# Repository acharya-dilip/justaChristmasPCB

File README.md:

# JustaChristmasPCB
This is a PCB with alternating green and red lights that turn on and off with a 0.6 second delay and has a hugeee snowflake in the back that'll be a challenge to me when I start soldering ;-;

# Schematic

# PCB

# 3D View

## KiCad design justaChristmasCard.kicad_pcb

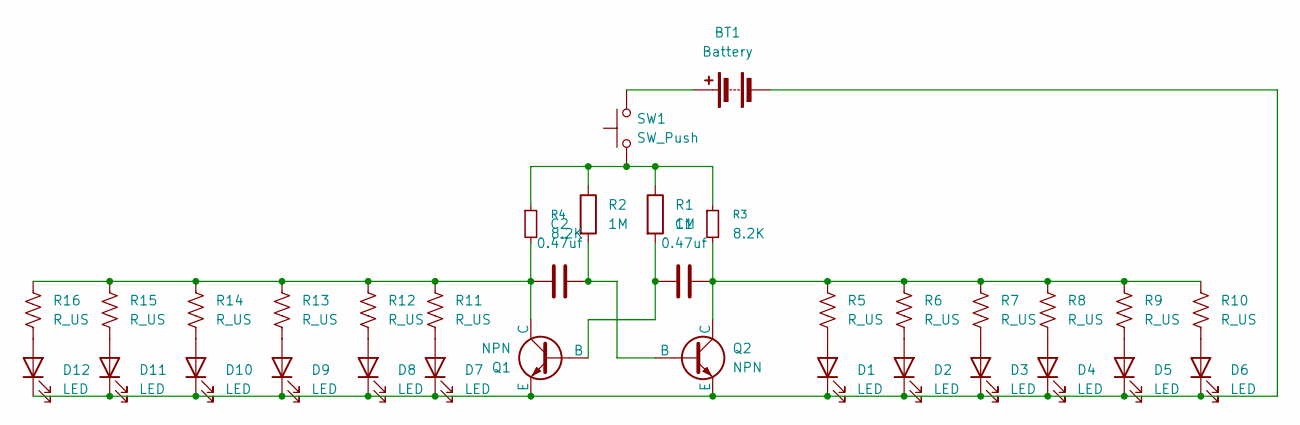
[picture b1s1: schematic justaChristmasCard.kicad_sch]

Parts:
BT1: Battery; PinHeader_1x02_P2.54mm_Vertical
C1, C2: 0.47uf; CP_Radial_D8.0mm_P5.00mm
D1, D2, D3, D4, D5, D6, D7, D8, D9, D10, D11, D12: LED; LED_D5.0mm
Q1, Q2: NPN; TO-92L_HandSolder
R1, R2: 1M; R_Axial_DIN0207_L6.3mm_D2.5mm_P7.62mm_Horizontal
R3, R4: 8.2K; R_Axial_DIN0207_L6.3mm_D2.5mm_P7.62mm_Horizontal
R5, R6, R7, R8, R9, R10, R11, R12, R13, R14, R15, R16: R_US; R_Axial_DIN0207_L6.3mm_D2.5mm_P7.62mm_Horizontal
SW1: SW_Push; SW_PUSH_6mm

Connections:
unnamed: BT1.1 (+), SW1.2
unnamed: BT1.2 (-), D1.1 (K), D2.1 (K), D3.1 (K), D4.1 (K), D5.1 (K), D6.1 (K), D7.1 (K), D8.1 (K), D9.1 (K), D10.1 (K), D11.1 (K), D12.1 (K), Q1.3 (E), Q2.3 (E)
unnamed: D1.2 (A), R5.2
unnamed: D2.2 (A), R6.2
unnamed: D3.2 (A), R7.2
unnamed: D4.2 (A), R8.2
unnamed: D5.2 (A), R9.2
unnamed: D6.2 (A), R10.2
unnamed: D7.2 (A), R11.2
unnamed: D8.2 (A), R12.2
unnamed: D9.2 (A), R13.2
unnamed: D10.2 (A), R14.2
unnamed: D11.2 (A), R15.2
unnamed: D12.2 (A), R16.2
unnamed: C1.1, Q1.2 (B), R1.2
unnamed: C2.1, Q1.1 (C), R4.2, R11.1, R12.1, R13.1, R14.1, R15.1, R16.1
unnamed: C2.2, Q2.2 (B), R2.2
unnamed: C1.2, Q2.1 (C), R3.2, R5.1, R6.1, R7.1, R8.1, R9.1, R10.1
unnamed: R1.1, R2.1, R3.1, R4.1, SW1.1

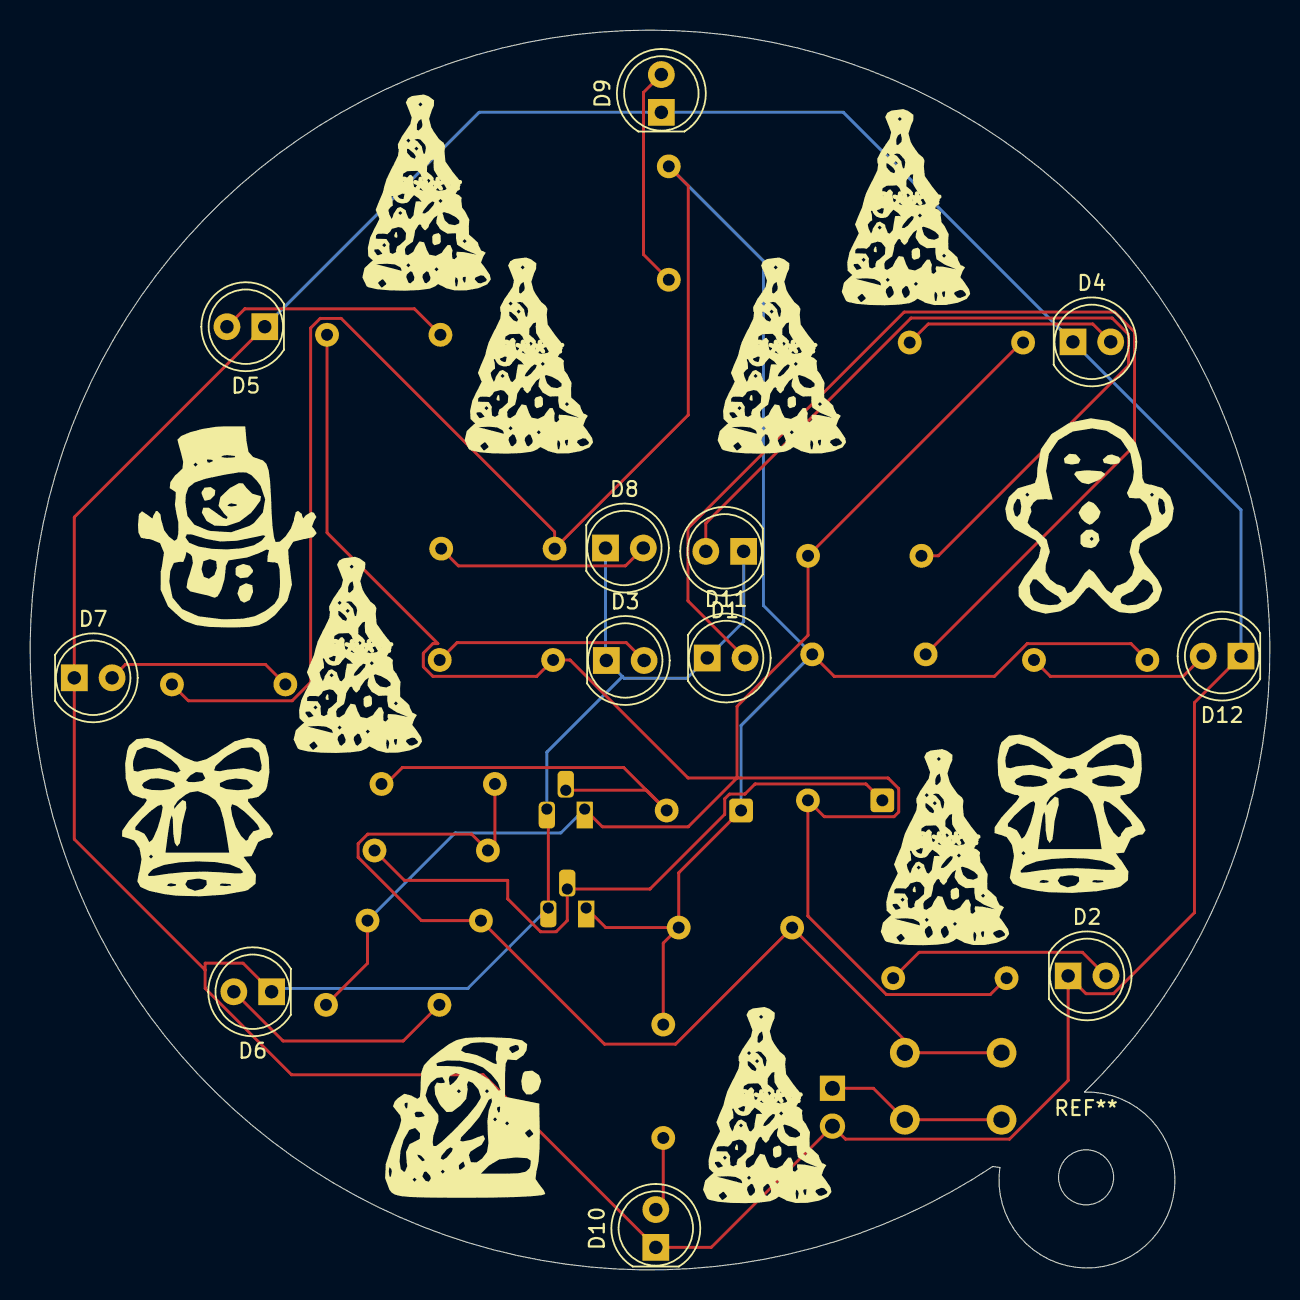
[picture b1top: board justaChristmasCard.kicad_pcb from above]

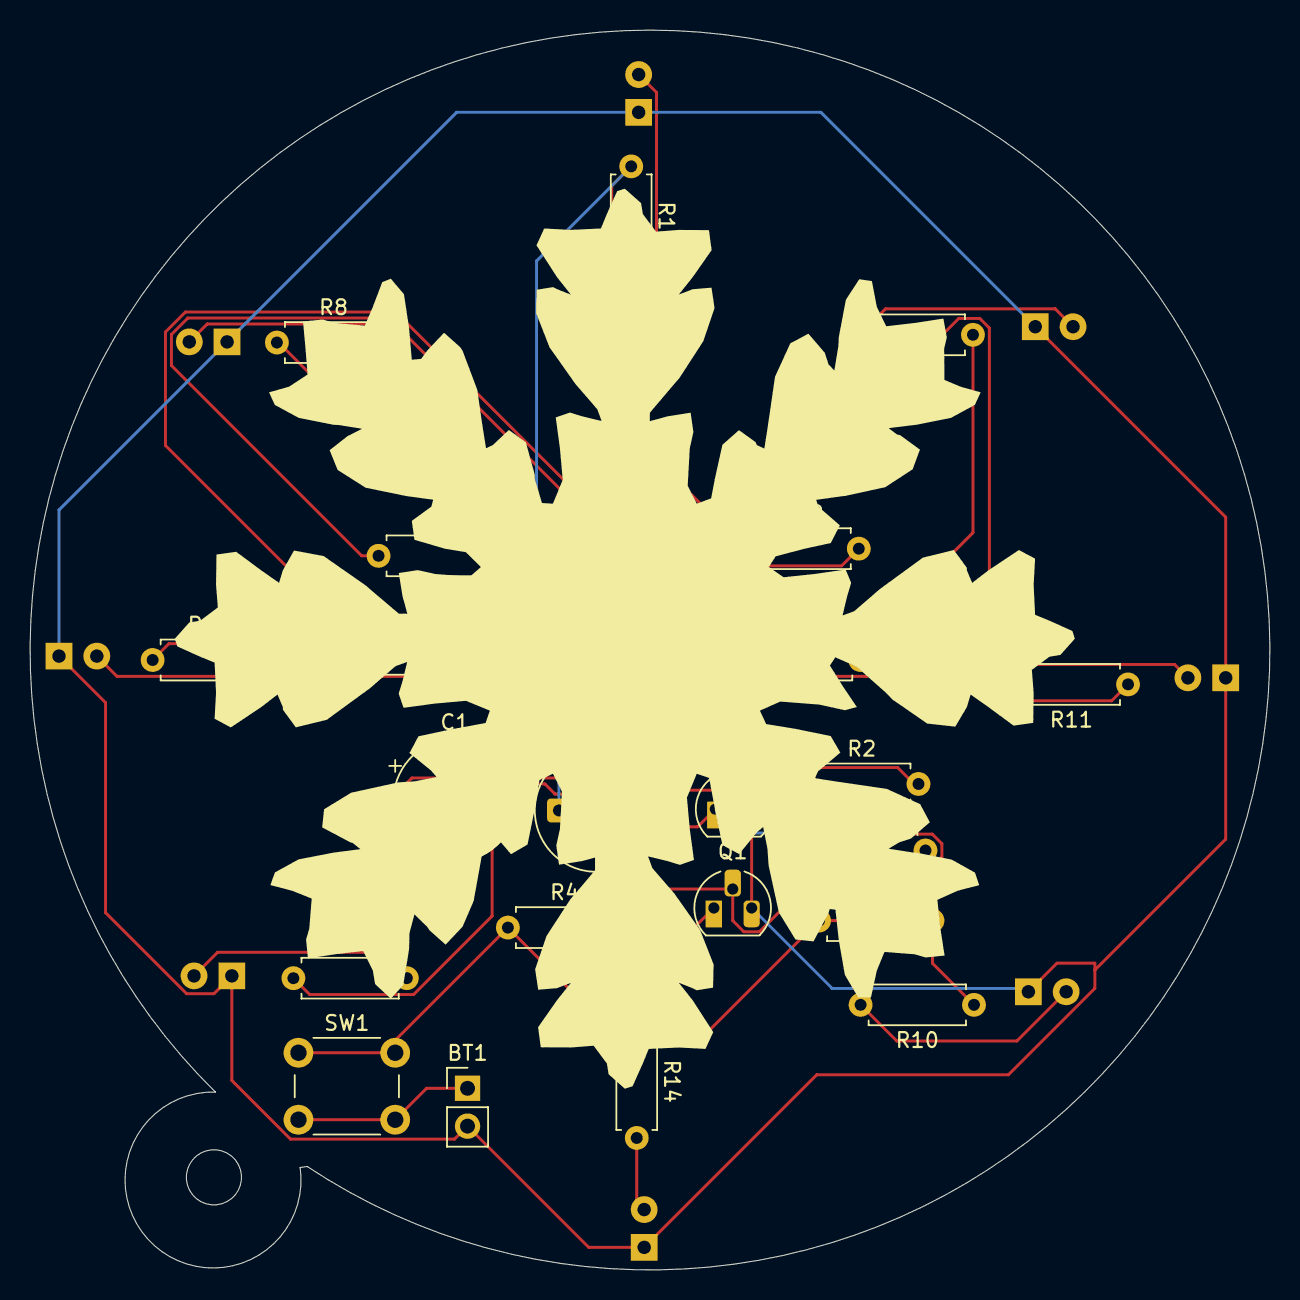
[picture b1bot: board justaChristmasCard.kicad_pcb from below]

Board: 2 copper layers, 83.3 x 83.3 mm, 34 parts (22 on the bottom side), 19 nets.

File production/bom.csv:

Designator,Footprint,Quantity,Value,LCSC Part #
BT1,PinHeader_1x02_P2.54mm_Vertical,1,Battery,
"C1, C2",CP_Radial_D8.0mm_P5.00mm,2,0.47uf,
"D1, D10, D11, D12, D2, D3, D4, D5, D6, D7, D8, D9",LED_D5.0mm,12,LED,
"Q1, Q2",TO-92L_HandSolder,2,NPN,
"R1, R2",R_Axial_DIN0207_L6.3mm_D2.5mm_P7.62mm_Horizontal,2,1M,
"R10, R11, R12, R13, R14, R15, R16, R5, R6, R7, R8, R9",R_Axial_DIN0207_L6.3mm_D2.5mm_P7.62mm_Horizontal,12,R_US,
"R3, R4",R_Axial_DIN0207_L6.3mm_D2.5mm_P7.62mm_Horizontal,2,8.2K,
SW1,SW_PUSH_6mm,1,SW_Push,

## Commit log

2025-12-15 pcb done
